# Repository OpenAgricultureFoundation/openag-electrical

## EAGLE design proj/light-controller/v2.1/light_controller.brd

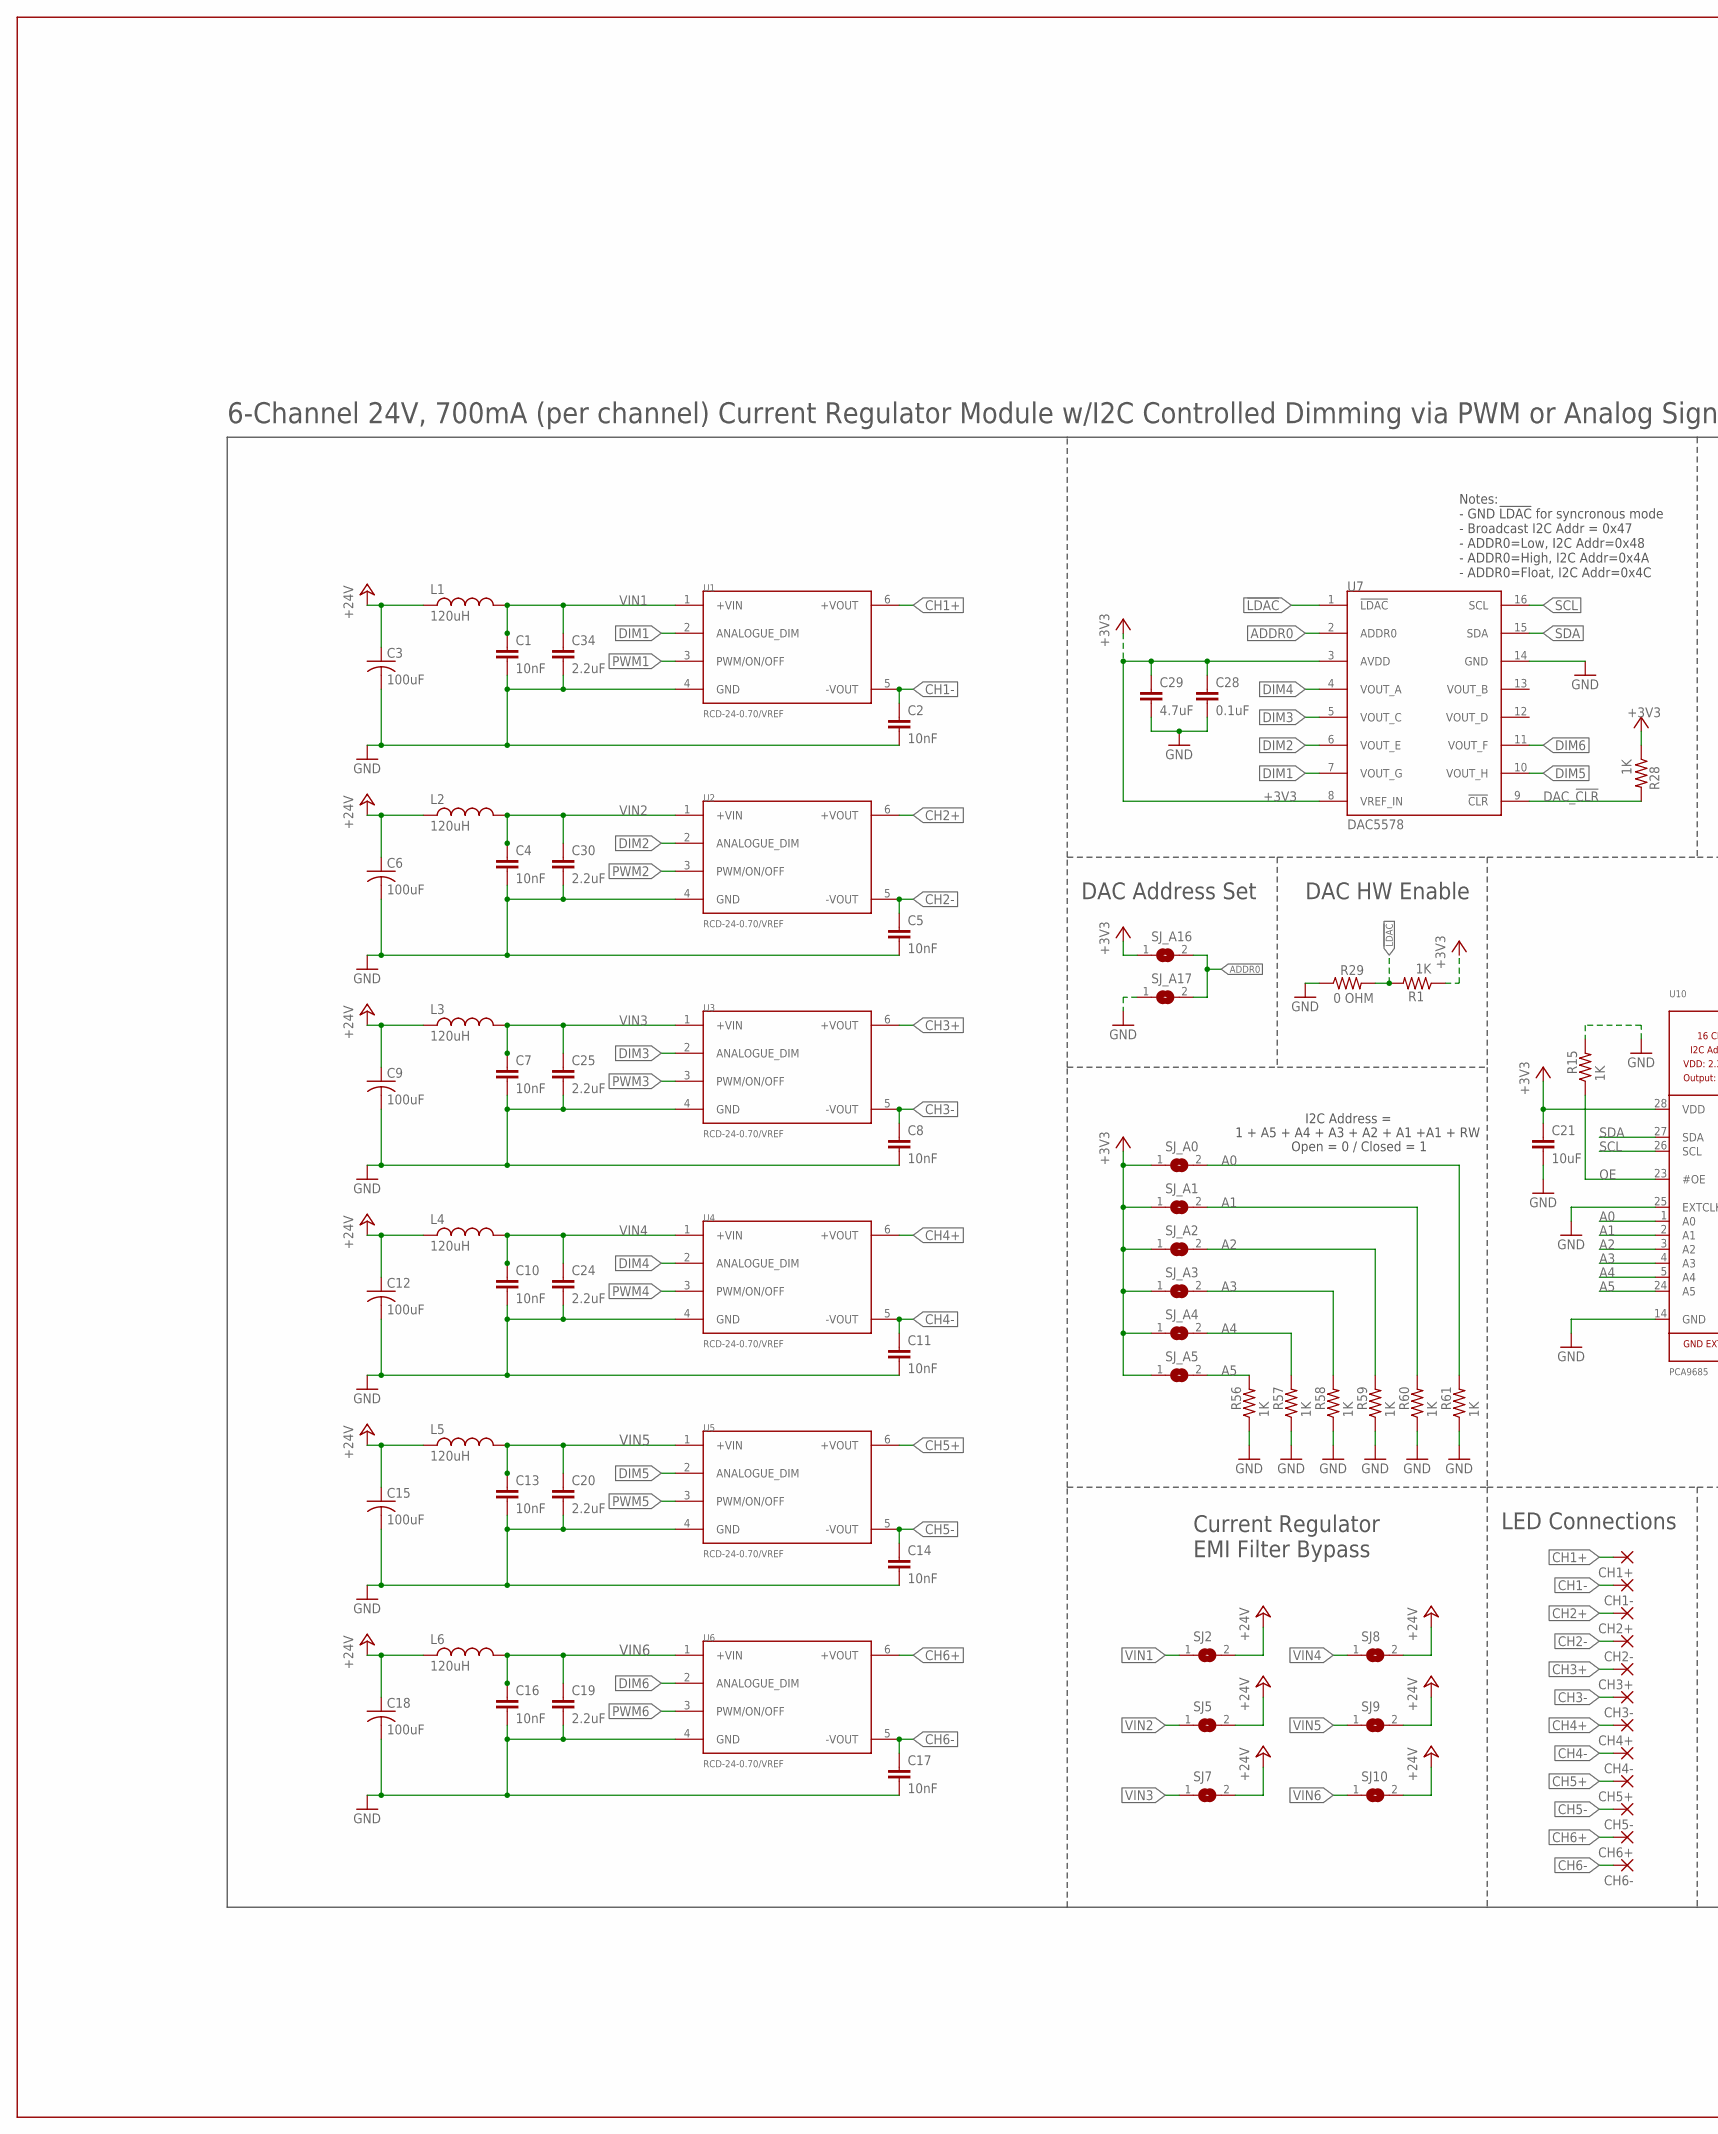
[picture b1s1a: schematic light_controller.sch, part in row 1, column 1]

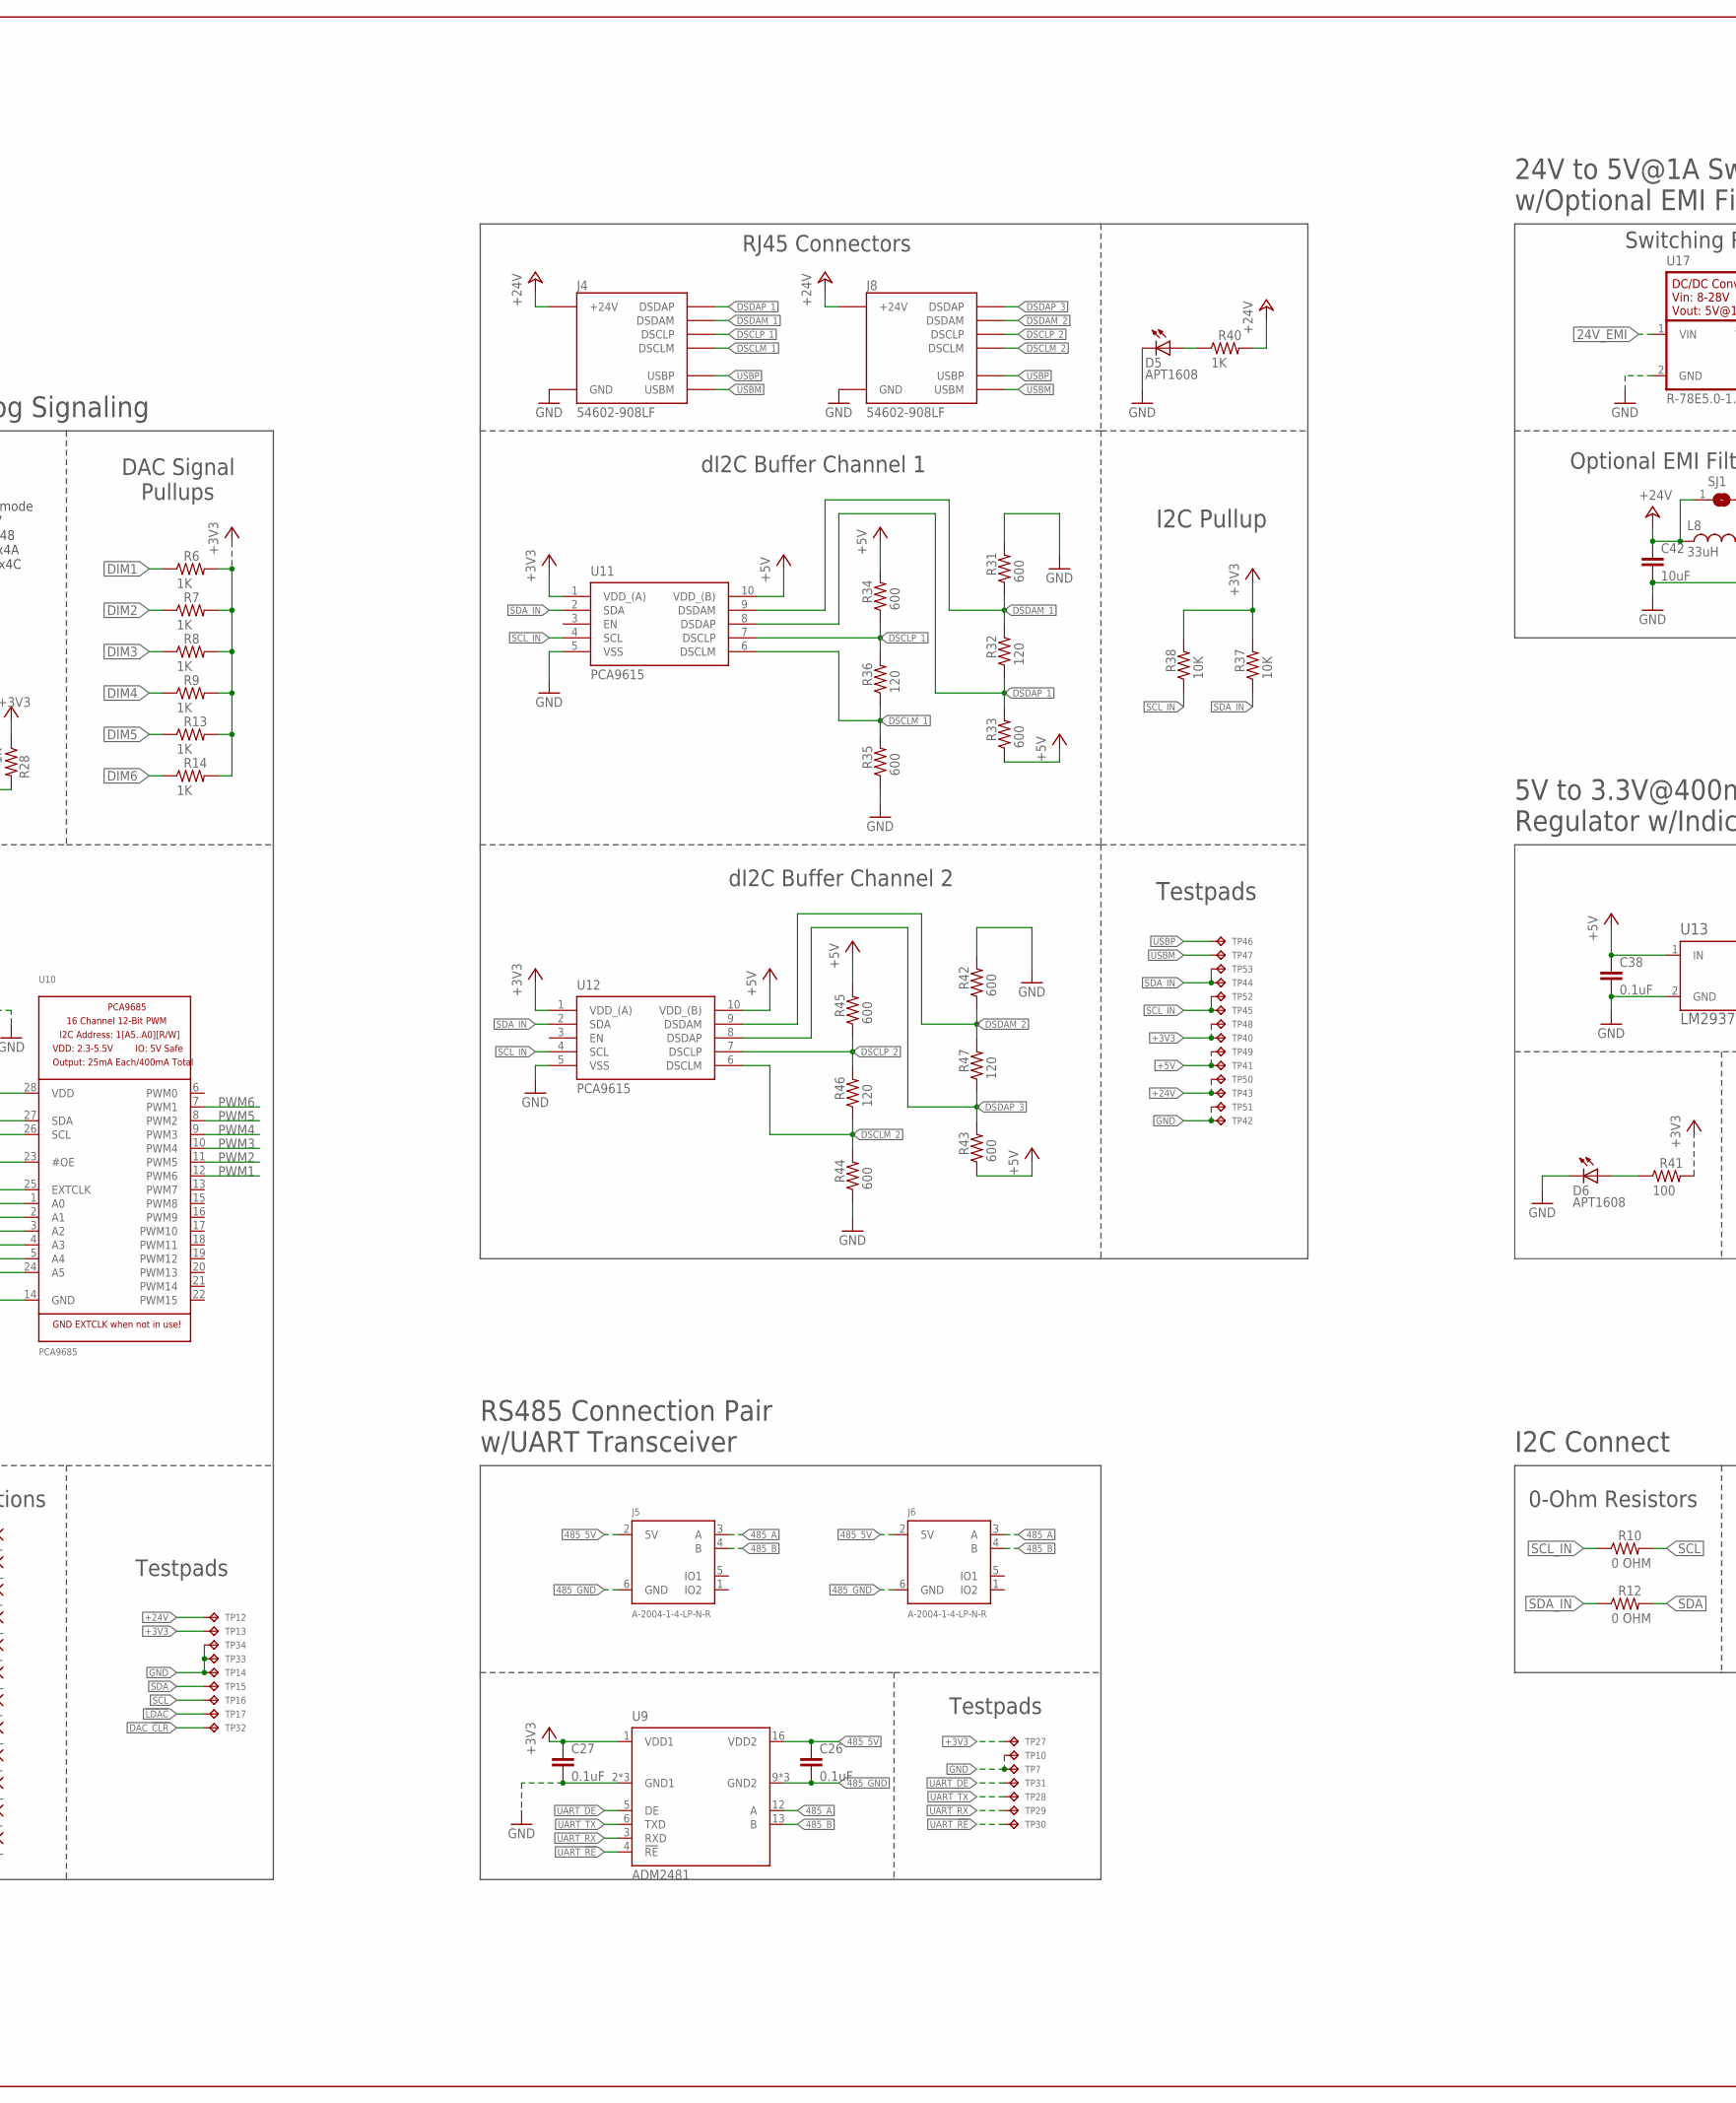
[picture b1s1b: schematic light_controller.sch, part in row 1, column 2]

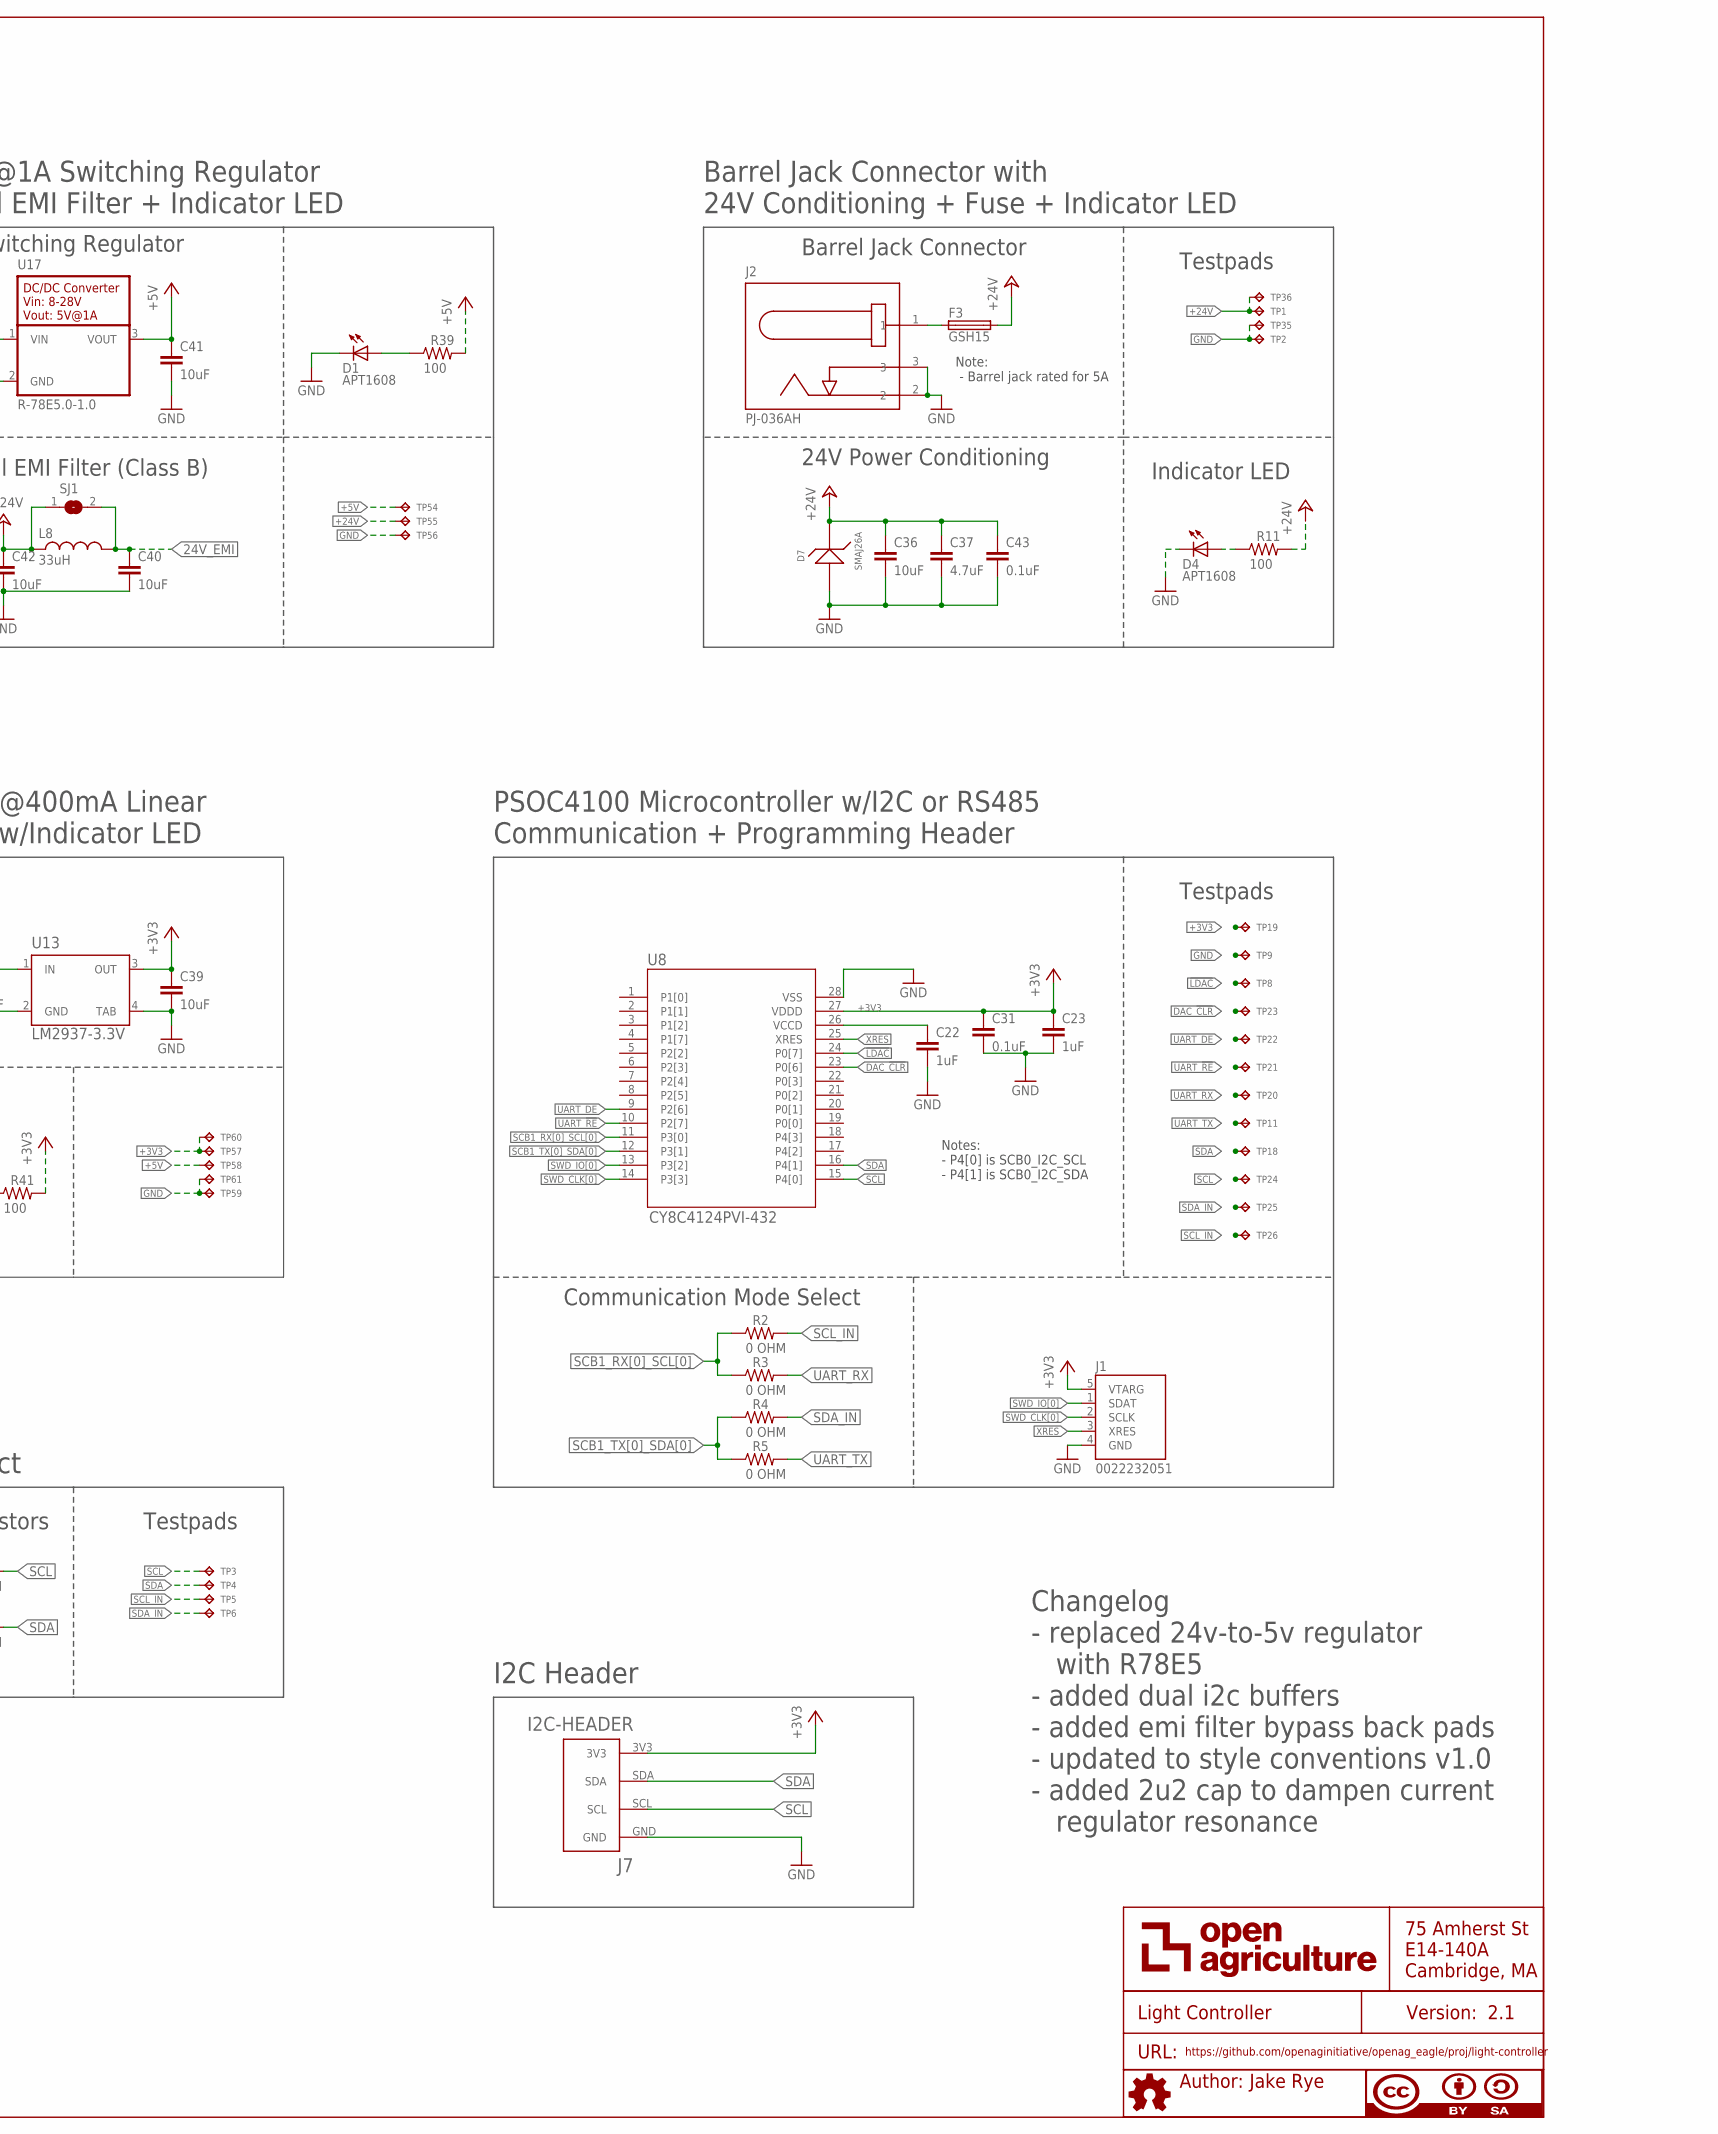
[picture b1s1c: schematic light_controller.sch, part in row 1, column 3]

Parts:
C1, C2, C4, C5, C7, C8, C10, C11, C13, C14, C16, C17: 10nF; C0603
C3, C6, C9, C12, C15, C18: 100uF; EEE-1HA101UP
C19, C20, C24, C25, C30, C34: 2.2uF; C0603
C21, C36, C39, C40, C41, C42: 10uF; C0805
C22, C23: 1uF; C0603
C26, C27, C28, C31, C38, C43: 0.1uF; C0603
C29, C37: 4.7uF; C0805
CH1+, CH1-, CH2+, CH2-, CH3+, CH3-, CH4+, CH4-, CH5+, CH5-, CH6+, CH6-: 3,17/1,3
D1, D4, D5, D6: APT1608; CHIPLED_0603
D7: SMAJ26A; SMA
F3: GSH15
J1: 0022232051; PSOC-PROGRAMMER-22-23-2051
J2: PJ-036AH; BARREL-JACK-PJ-036AH
J4, J8: 54602-908LF; RJ45-DI2C-USB-54602-908LF
J5, J6: A-2004-1-4-LP-N-R; RJ12-RS485--A-2004-1-4-LP-N-R
J7: I2C-HEADER; HEADER-I2C
L1, L2, L3, L4, L5, L6: 120uH; 74404064121
L8: 33uH; 29333C
R1, R6, R7, R8, R9, R13, R14, R15, R28, R40, R56, R57, R58, R59, R60, R61: 1K; RC0603N
R2, R3, R4, R5, R10, R12, R29: 0 OHM; RC0603N
R11, R39, R41: 100; RC0603N
R31, R33, R34, R35, R42, R43, R44, R45: 600; RC0603N
R32, R36, R46, R47: 120; RC0603N
R37, R38: 10K; RC0603N
SJ1, SJ2, SJ5, SJ7, SJ8, SJ9, SJ10: EMI-BYPASS
SJ_A0, SJ_A1, SJ_A2, SJ_A3, SJ_A4, SJ_A5, SJ_A16, SJ_A17: SOLDERJUMPERREFLOW_NOPASTE; SJ1
TP1, TP2, TP3, TP4, TP5, TP6, TP7, TP8, TP9, TP10, TP11, TP12, TP13, TP14, TP15, TP16, TP17, TP18, TP19, TP20, TP21, TP22, TP23, TP24, TP25, TP26, TP27, TP28, TP29, TP30, TP31, TP32, TP33, TP34, TP35, TP36, TP40, TP41, TP42, TP43, TP44, TP45, TP46, TP47, TP48, TP49, TP50, TP51, TP52, TP53, TP57, TP58, TP59, TP60, TP61: TPTP04R; TP04R
TP54, TP55, TP56: TPTP06R; TP06R
U1, U2, U3, U4, U5, U6: RCD-24-0.70/VREF; RCD-24-PINNED
U7: DAC5578; TSSOP16
U8: CY8C4124PVI-432; SSOP-28
U9: ADM2481; SOIC16LWB
U10: PCA9685; TSSOP28
U11, U12: PCA9615; SOP50P490X110-10N
U13: LM2937-3.3V; MP04A
U17: R-78E5.0-1.0
U$6: AUTHOR
U$7: TITLE

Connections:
24V_EMI: C40.1, L8.2, SJ1.2, U17.1 (VIN)
24V_IN: F3.1, J2.1
485_5V: C26.1, J5.2 (5V), J6.2 (5V), U9.16 (VDD2)
485_A: J5.3 (A), J6.3 (A), U9.12 (A)
485_B: J5.4 (B), J6.4 (B), U9.13 (B)
485_GND: C26.2, J5.6 (GND), J6.6 (GND), U9.9 (GND2), U9.10 (GND2), U9.15 (GND2)
!LDAC!: R1.2, R29.2, TP8.1, TP17.1, U7.1 (!LDAC!), U8.24 (P0[7])
+3V3: C21.1, C23.1, C27.1, C28.1, C29.1, C31.1, C39.1, J1.5 (VTARG), J7.3V3, R1.1, R6.2, R7.2, R8.2, R9.2, R13.2, R14.2, R28.1, R37.2, R38.2, R41.2, SJ_A0.1, SJ_A1.1, SJ_A2.1, SJ_A3.1, SJ_A4.1, SJ_A5.1, SJ_A16.1, TP13.1, TP19.1, TP27.1, TP40.1, TP48.1, TP57.1, TP60.1, U7.3 (AVDD), U7.8 (VREF_IN), U8.27 (VDDD), U9.1 (VDD1), U10.28 (VDD), U11.1 (VDD_(A)), U12.1 (VDD_(A)), U13.3 (OUT)
+5V: C38.1, C41.1, R33.1, R34.2, R39.2, R43.1, R45.2, TP41.1, TP49.1, TP54.TP, TP58.1, U11.10 (VDD_(B)), U12.10 (VDD_(B)), U13.1 (IN), U17.3 (VOUT)
+24V: C3.+ (1(+)), C6.+ (1(+)), C9.+ (1(+)), C12.+ (1(+)), C15.+ (1(+)), C18.+ (1(+)), C36.1, C37.1, C42.1, C43.1, D7.1, F3.2, J4.24V(6) (+24V), J8.24V(6) (+24V), L1.1, L2.1, L3.1, L4.1, L5.1, L6.1, L8.1, R11.2, R40.2, SJ1.1, SJ2.2, SJ5.2, SJ7.2, SJ8.2, SJ9.2, SJ10.2, TP1.1, TP12.1, TP36.1, TP43.1, TP50.1, TP55.TP
A0: R61.2, SJ_A0.2, U10.1 (A0)
A1: R60.2, SJ_A1.2, U10.2 (A1)
A2: R59.2, SJ_A2.2, U10.3 (A2)
A3: R58.2, SJ_A3.2, U10.4 (A3)
A4: R57.2, SJ_A4.2, U10.5 (A4)
A5: R56.2, SJ_A5.2, U10.24 (A5)
ADDR0: SJ_A16.2, SJ_A17.2, U7.2 (ADDR0)
CH1+: CH1+.1, U1.6 (+VOUT)
CH1-: C2.1, CH1-.1, U1.5 (-VOUT)
CH2+: CH2+.1, U2.6 (+VOUT)
CH2-: C5.1, CH2-.1, U2.5 (-VOUT)
CH3+: CH3+.1, U3.6 (+VOUT)
CH3-: C8.1, CH3-.1, U3.5 (-VOUT)
CH4+: CH4+.1, U4.6 (+VOUT)
CH4-: C11.1, CH4-.1, U4.5 (-VOUT)
CH5+: CH5+.1, U5.6 (+VOUT)
CH5-: C14.1, CH5-.1, U5.5 (-VOUT)
CH6+: CH6+.1, U6.6 (+VOUT)
CH6-: C17.1, CH6-.1, U6.5 (-VOUT)
DAC_!CLR!: R28.2, TP23.1, TP32.1, U7.9 (!CLR!), U8.23 (P0[6])
DIM1: R6.1, U1.2 (ANALOGUE_DIM), U7.7 (VOUT_G)
DIM2: R7.1, U2.2 (ANALOGUE_DIM), U7.6 (VOUT_E)
DIM3: R8.1, U3.2 (ANALOGUE_DIM), U7.5 (VOUT_C)
DIM4: R9.1, U4.2 (ANALOGUE_DIM), U7.4 (VOUT_A)
DIM5: R13.1, U5.2 (ANALOGUE_DIM), U7.10 (VOUT_H)
DIM6: R14.1, U6.2 (ANALOGUE_DIM), U7.11 (VOUT_F)
DSCLM_1: J4.DSCLM(5) (DSCLM), R35.2, R36.1, U11.6 (DSCLM)
DSCLM_2: J8.DSCLM(5) (DSCLM), R44.2, R46.1, U12.6 (DSCLM)
DSCLP_1: J4.DSCLP(4) (DSCLP), R34.1, R36.2, U11.7 (DSCLP)
DSCLP_2: J8.DSCLP(4) (DSCLP), R45.1, R46.2, U12.7 (DSCLP)
DSDAM_1: J4.DSDAM(2) (DSDAM), R31.1, R32.2, U11.9 (DSDAM)
DSDAM_2: J8.DSDAM(2) (DSDAM), R42.1, R47.2, U12.9 (DSDAM)
DSDAP_1: J4.DSDAP(1) (DSDAP), R32.1, R33.2, U11.8 (DSDAP)
DSDAP_3: J8.DSDAP(1) (DSDAP), R43.2, R47.1, U12.8 (DSDAP)
GND: C1.2, C2.2, C3.- (2(-)), C4.2, C5.2, C6.- (2(-)), C7.2, C8.2, C9.- (2(-)), C10.2, C11.2, C12.- (2(-)), C13.2, C14.2, C15.- (2(-)), C16.2, C17.2, C18.- (2(-)), C19.2, C20.2, C21.2, C22.2, C23.2, C24.2, C25.2, C27.2, C28.2, C29.2, C30.2, C31.2, C34.2, C36.2, C37.2, C38.2, C39.2, C40.2, C41.2, C42.2, C43.2, D1.C, D4.C, D5.C, D6.C, D7.2, J1.4 (GND), J2.2, J2.3, J4.GND(3) (GND), J7.GND, J8.GND(3) (GND), R15.2, R29.1, R31.2, R35.1, R42.2, R44.1, R56.1, R57.1, R58.1, R59.1, R60.1, R61.1, SJ_A17.1, TP2.1, TP7.1, TP9.1, TP10.1, TP14.1, TP33.1, TP34.1, TP35.1, TP42.1, TP51.1, TP56.TP, TP59.1, TP61.1, U1.4 (GND), U2.4 (GND), U3.4 (GND), U4.4 (GND), U5.4 (GND), U6.4 (GND), U7.14 (GND), U8.28 (VSS), U9.2 (GND1), U9.7 (GND1), U9.8 (GND1), U10.14 (GND), U10.25 (EXTCLK), U11.5 (VSS), U12.5 (VSS), U13.2 (GND), U13.4 (TAB), U17.2 (GND)
unnamed: D1.A, R39.1
unnamed: D5.A, R40.1
unnamed: D6.A, R41.1
unnamed: D4.A, R11.1
unnamed: C22.1, U8.26 (VCCD)
OE: R15.1, U10.23 (#OE)
PWM1: U1.3 (PWM/ON/OFF), U10.12 (PWM6)
PWM2: U2.3 (PWM/ON/OFF), U10.11 (PWM5)
PWM3: U3.3 (PWM/ON/OFF), U10.10 (PWM4)
PWM4: U4.3 (PWM/ON/OFF), U10.9 (PWM3)
PWM5: U5.3 (PWM/ON/OFF), U10.8 (PWM2)
PWM6: U6.3 (PWM/ON/OFF), U10.7 (PWM1)
SCB1_RX[0]_SCL[0]: R2.1, R3.1, U8.11 (P3[0])
SCB1_TX[0]_SDA[0]: R4.1, R5.1, U8.12 (P3[1])
SCL: J7.SCL, R10.2, TP3.1, TP16.1, TP24.1, U7.16 (SCL), U8.15 (P4[0]), U10.26 (SCL)
SCL_IN: R2.2, R10.1, R38.1, TP5.1, TP26.1, TP45.1, TP52.1, U11.4 (SCL), U12.4 (SCL)
SDA: J7.SDA, R12.2, TP4.1, TP15.1, TP18.1, U7.15 (SDA), U8.16 (P4[1]), U10.27 (SDA)
SDA_IN: R4.2, R12.1, R37.1, TP6.1, TP25.1, TP44.1, TP53.1, U11.2 (SDA), U12.2 (SDA)
SWD_CLK[0]: J1.2 (SCLK), U8.14 (P3[3])
SWD_IO[0]: J1.1 (SDAT), U8.13 (P3[2])
UART_!RE!: TP21.1, TP30.1, U8.10 (P2[7]), U9.4 (!RE!)
UART_DE: TP22.1, TP31.1, U8.9 (P2[6]), U9.5 (DE)
UART_RX: R3.2, TP20.1, TP29.1, U9.3 (RXD)
UART_TX: R5.2, TP11.1, TP28.1, U9.6 (TXD)
USBM: J4.USBM(8) (USBM), J8.USBM(8) (USBM), TP47.1
USBP: J4.USBP(7) (USBP), J8.USBP(7) (USBP), TP46.1
VIN1: C1.1, C34.1, L1.2, SJ2.1, U1.1 (+VIN)
VIN2: C4.1, C30.1, L2.2, SJ5.1, U2.1 (+VIN)
VIN3: C7.1, C25.1, L3.2, SJ7.1, U3.1 (+VIN)
VIN4: C10.1, C24.1, L4.2, SJ8.1, U4.1 (+VIN)
VIN5: C13.1, C20.1, L5.2, SJ9.1, U5.1 (+VIN)
VIN6: C16.1, C19.1, L6.2, SJ10.1, U6.1 (+VIN)
XRES: J1.3 (XRES), U8.25 (XRES)

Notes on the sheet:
Notes: - GND !LDAC! for syncronous mode - Broadcast I2C Addr = 0x47 - ADDR0=Low, I2C Addr=0x48 - ADDR0=High, I2C Addr=0x4A - ADDR0=Float, I2C Addr=0x4C
1 + A5 + A4 + A3 + A2 + A1 +A1 + RW
I2C Address =
Open = 0 / Closed = 1
RS485 Connection Pair w/UART Transceiver
PSOC4100 Microcontroller w/I2C or RS485 Communication + Programming Header
I2C Header
6-Channel 24V, 700mA (per channel) Current Regulator Module w/I2C Controlled Dimming via PWM or Analog Signaling
Changelog - replaced 24v-to-5v regulator with R78E5 - added dual i2c buffers - added emi filter bypass back pads - updated to style conventions v1.0 - added 2u2 cap to dampen current regulator resonance
Notes: - P4[0] is SCB0_I2C_SCL - P4[1] is SCB0_I2C_SDA
Communication Mode Select
I2C Connect
Testpads
Current Regulator EMI Filter Bypass
5V to 3.3V@400mA Linear Regulator w/Indicator LED
dI2C Buffer Channel 1
RJ45 Connectors
24V to 5V@1A Switching Regulator w/Optional EMI Filter + Indicator LED
Switching Regulator
Optional EMI Filter (Class B)
dI2C Buffer Channel 2
I2C Pullup
Barrel Jack Connector
Barrel Jack Connector with 24V Conditioning + Fuse + Indicator LED
24V Power Conditioning
Indicator LED
0-Ohm Resistors
LED Connections
DAC Signal Pullups
DAC Address Set
DAC HW Enable
Note: - Barrel jack rated for 5A

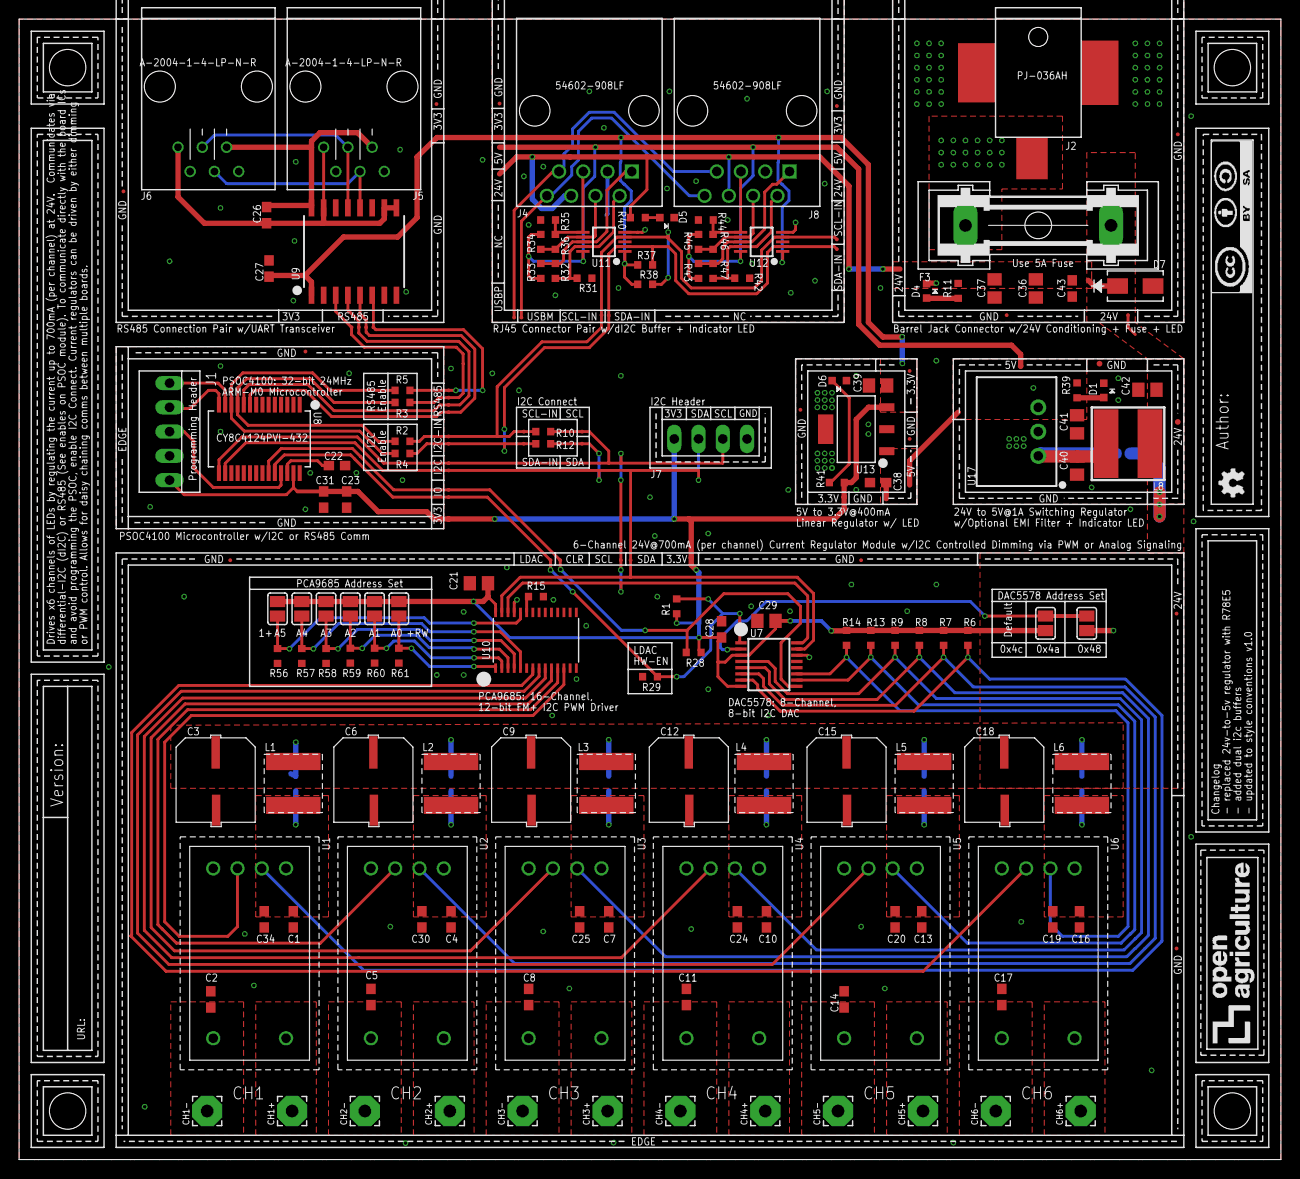
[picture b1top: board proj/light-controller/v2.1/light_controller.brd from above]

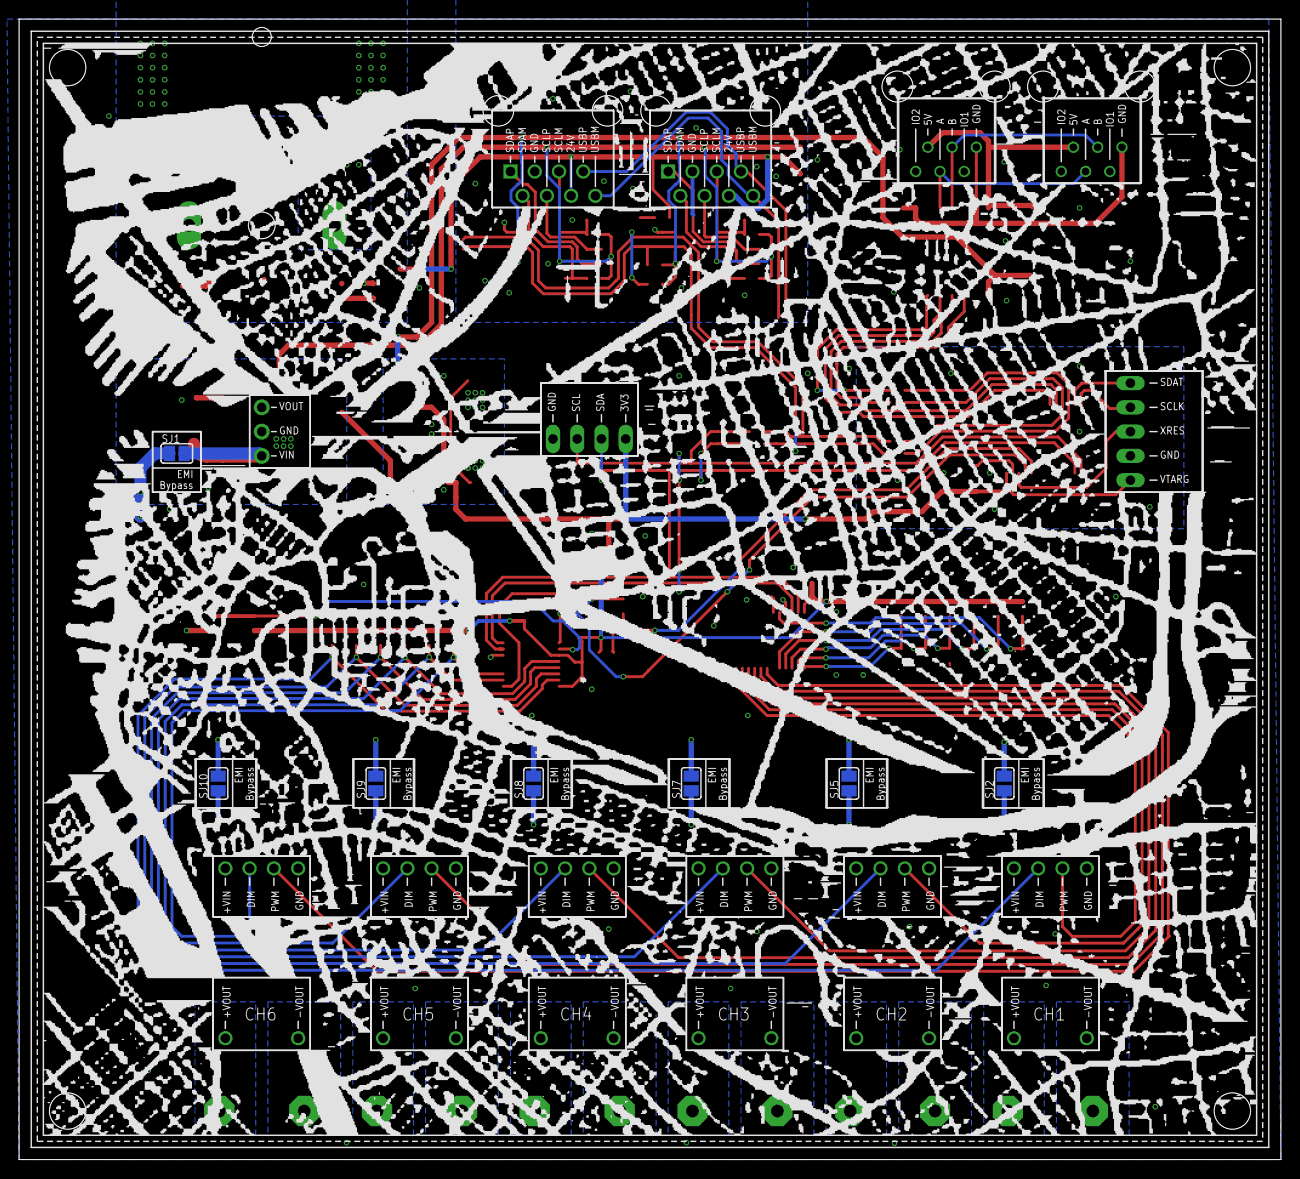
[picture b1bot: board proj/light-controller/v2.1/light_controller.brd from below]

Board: 2 copper layers, 132.1 x 119.4 mm, 207 parts (7 on the bottom side), 78 nets.

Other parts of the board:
U$1, U$2, U$3, U$4: CORNER
U$8: LOGO
U$9: CAMBRIDGE-MAP-LIGHT-CONTROLLER-V-2-1

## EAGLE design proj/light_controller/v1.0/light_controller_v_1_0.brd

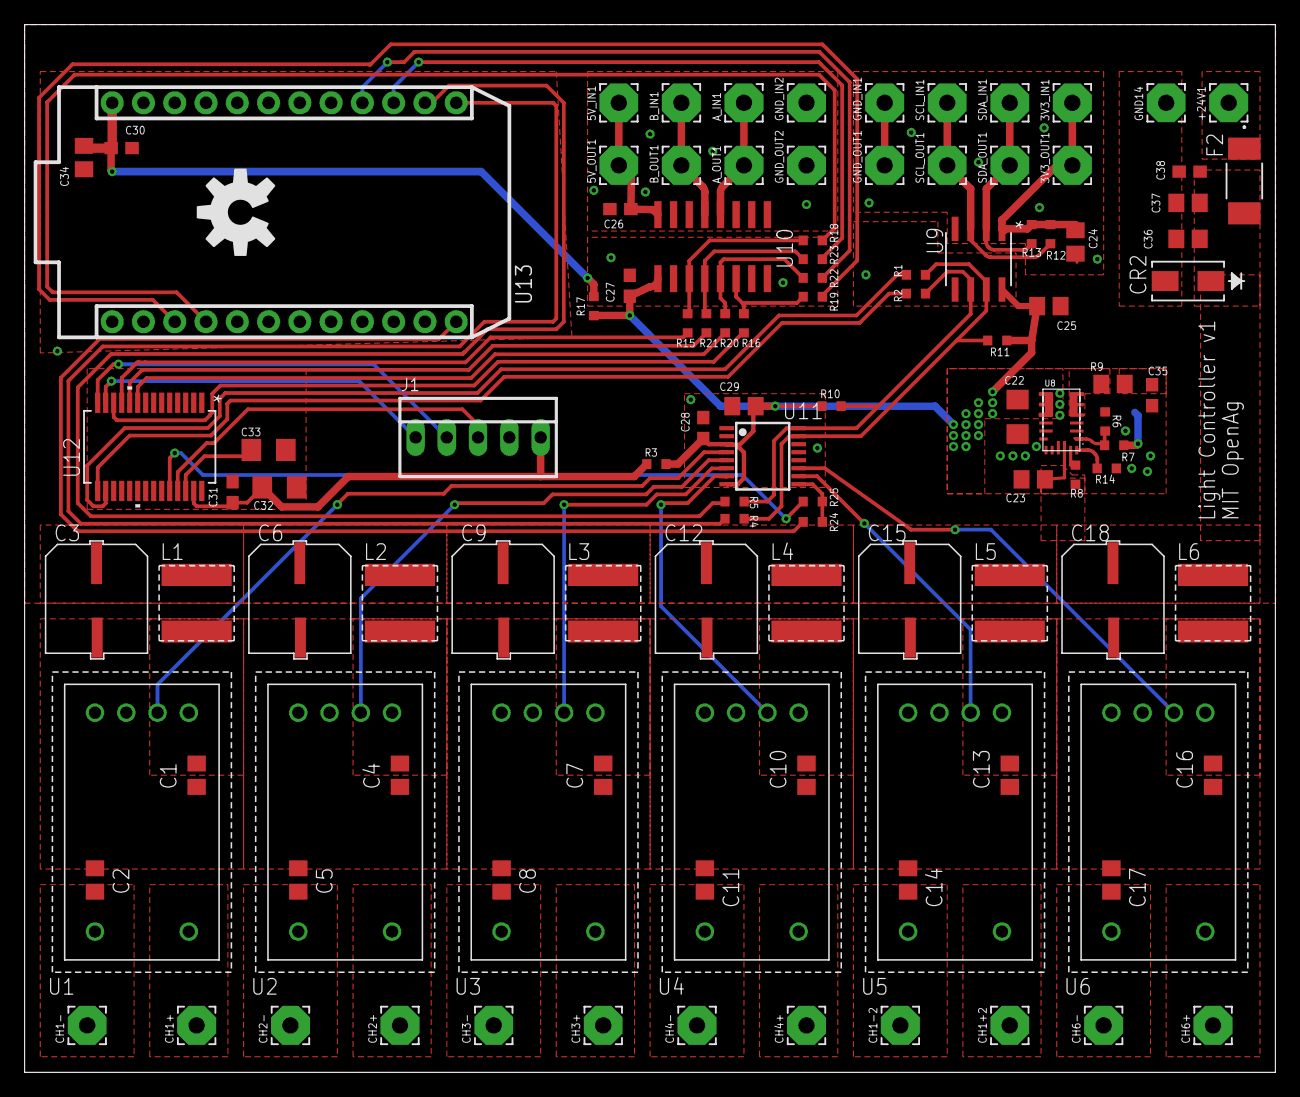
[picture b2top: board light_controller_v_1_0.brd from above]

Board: 2 copper layers, 101.6 x 85.1 mm, 112 parts (0 on the bottom side), 68 nets.

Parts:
3V3_IN1, 3V3_OUT1, 5V_IN1, 5V_OUT1: 3,17/1,3
+24V1: 3,17/1,3
A_IN1: 3,17/1,3
A_OUT1: 3,17/1,3
B_IN1: 3,17/1,3
B_OUT1: 3,17/1,3
C1, C2, C4, C5, C7, C8, C10, C11, C13, C14, C16, C17, C23, C24, C25, C36: 10uF; C0805
C3, C6, C9, C12, C15, C18: 100uF; EEE-1HA101UP
C22: 22uF; C1206
C26, C27, C28, C30, C31, C38: 0.1uF; C0603
C29, C34, C37: 4.7uF; C0805
C32, C33: 1uF; C1206
C35: 330pF; C0603
CH1+, CH1+2, CH1-, CH1-2, CH2+, CH2-, CH3+, CH3-, CH4+, CH4-, CH6+, CH6-: 3,17/1,3
CR2: SMAJ26A-13-F; SMA
F2: SST 7; SS
GND14: 3,17/1,3
GND_IN1, GND_IN2: 3,17/1,3
GND_OUT1, GND_OUT2: 3,17/1,3
J1: 0022232051; 22-23-2051
L1, L2, L3, L4, L5, L6: 120uH; 74404064121
LOGO1: OSHW-LOGOL; OSHW-LOGO-L
R1, R2, R3, R4, R5, R15, R16, R17, R18, R19, R20, R21, R22, R23, R24, R25: 0 OHM; RC0603N
R6: 51K; RC0603N
R7: 160K; RC0603N
R8: 200K; RC0603N
R9: 6.34 ohm; R0805
R10, R11, R12, R13: 1K; RC0603N
R14: 16.5K; RC0603N
SCL_IN1: 3,17/1,3
SCL_OUT1: 3,17/1,3
SDA_IN1: 3,17/1,3
SDA_OUT1: 3,17/1,3
U1, U2, U3, U4, U5, U6: RCD-24-0.70; RCD-24-PINNED
U8: MPM3620GQV-P; 20-POWERLFQFN-MODULE
U9: ISO1540DR; D8
U10: ADM2481BRWZ-RL7; SOIC16N
U11: DAC5578SPW; TSSOP16
U12: CY8C4124PVI-432; SSOP-28
U13: PHOTONH; PHOTON

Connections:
24V_IN: +24V1.1, F2.1
485_5V: 5V_IN1.1, 5V_OUT1.1, C26.1, U10.16
485_A: A_IN1.1, A_OUT1.1, U10.12
485_B: B_IN1.1, B_OUT1.1, U10.13
485_GND: C26.2, GND_IN2.1, GND_OUT2.1, U10.9, U10.10, U10.15
+3V3: C22.1, C25.1, C27.1, C28.1, C29.1, R3.1, R7.2, R10.2, R11.2, R17.2, U8.8, U9.8, U10.1, U11.3, U11.8
+24V: C3.+, C6.+, C9.+, C12.+, C15.+, C18.+, C23.1, C36.1, C37.1, C38.1, CR2.1, F2.2, L1.1, L2.1, L3.1, L4.1, L5.1, L6.1, R8.2, U8.16
CH1+: CH1+.1, U1.6
CH1-: C2.1, CH1-.1, U1.5
CH2+: CH2+.1, U2.6
CH2-: C5.1, CH2-.1, U2.5
CH3+: CH3+.1, U3.6
CH3-: C8.1, CH3-.1, U3.5
CH4+: CH4+.1, U4.6
CH4-: C11.1, CH4-.1, U4.5
CH5+: CH1+2.1, U5.6
CH5-: C14.1, CH1-2.1, U5.5
CH6+: CH6+.1, U6.6
CH6-: C17.1, CH6-.1, U6.5
DAC_!CLR!: R24.2, R25.2, U11.9
DIM1: U1.2, U11.4
DIM2: U2.2, U11.5
DIM3: U3.2, U11.6
DIM4: U4.2, U11.7
DIM5: U5.2, U11.10
DIM6: U6.2, U11.11
GND: C1.2, C2.2, C3.-, C4.2, C5.2, C6.-, C7.2, C8.2, C9.-, C10.2, C11.2, C12.-, C13.2, C14.2, C15.-, C16.2, C17.2, C18.-, C22.2, C23.2, C25.2, C27.2, C28.2, C29.2, C30.2, C31.2, C32.2, C33.2, C34.2, C35.2, C36.2, C37.2, C38.2, CR2.2, GND14.1, J1.4, R6.1, R14.1, U1.4, U2.4, U3.4, U4.4, U5.4, U6.4, U8.3, U8.12, U8.13, U8.14, U9.5, U10.2, U10.7, U10.8, U11.1, U11.14, U12.28, U13.2, U13.21
I2C_3V3: 3V3_IN1.1, 3V3_OUT1.1, C24.1, R12.2, R13.2, U9.1
I2C_GND: C24.2, GND_IN1.1, GND_OUT1.1, U9.4
I2C_SCL: R12.1, SCL_IN1.1, SCL_OUT1.1, U9.3
I2C_SDA: R13.1, SDA_IN1.1, SDA_OUT1.1, U9.2
unnamed: C1.1, L1.2, U1.1
unnamed: C4.1, L2.2, U2.1
unnamed: C7.1, L3.2, U3.1
unnamed: C10.1, L4.2, U4.1
unnamed: C13.1, L5.2, U5.1
unnamed: C16.1, L6.2, U6.1
unnamed: C30.1, C34.1, R17.1, U13.24
unnamed: R8.1, U8.17
unnamed: R6.2, R7.1, U8.1
unnamed: R9.2, U8.5
unnamed: C35.1, R9.1
unnamed: C33.1, U12.26
unnamed: R14.2, U8.18
P0[7]: R25.1, U12.24
P2[6]: R20.1, U12.9
P2[7]: R21.1, U12.10
PHOTON_A0: R24.1, U13.12
PHOTON_D2: R23.1, U13.15
PHOTON_D3: R22.1, U13.16
PHOTON_RX: R18.1, U13.4
PHOTON_SCL: R5.1, U13.14
PHOTON_SDA: R4.1, U13.13
PHOTON_TX: R19.1, U13.3
SCB0_I2C_SCL: R2.1, U12.15
SCB0_I2C_SDA: R1.1, U12.16
SCB1_RX[0]: R15.1, U12.11
SCB1_TX[0]: R16.1, U12.12
SCL: R2.2, R5.2, R10.1, U9.6, U11.16
SDA: R1.2, R4.2, R11.1, U9.7, U11.15
SWD_CLK[0]: J1.2, U12.14
SWD_IO[0]: J1.1, U12.13
UART_!RE!: R21.2, R23.2, U10.4
UART_DE: R20.2, R22.2, U10.5
UART_RX: R15.2, R18.2, U10.3
UART_TX: R16.2, R19.2, U10.6
VDDD: C31.1, C32.1, J1.5, R3.2, U12.27
XRES: J1.3, U12.25

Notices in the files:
parts and their libraries:
SparkFun-Aesthetics: Licensing: Creative Commons ShareAlike 4.0 International - https://creativecommons.org/licenses/by-sa/4.0
